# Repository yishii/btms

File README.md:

# Back To the Meeting Switch (BTMS) 【緊急】会議復帰スイッチ

[[日本語版はこちら]](README_ja.md)

## Back Story
Sometimes happen that attending to the online meeting that roughly just listen to. 
This  is the chance for do editing excel or powerpoints.

But, if suddenly asked some comment unexpectedly, then in panic and cannot back to the meeting right away quickly.

That's why we developed Back To the Meeting Switch(BTMS) for this solution.

With the BTMS, you can turn the knob to select the backgrounded online meeting window, then press the knob the meeting windows comes to the forefront, and at the same time, the MIC mute turns off. And just you do is answer with relax.

So, ~~do another job~~ attend the meeting in peace.

## What is BTMS?

BTMS (Back To the Meeting Switch) is a kind of human interface device that using Seeeduino Xiao (SAMD or RP2040).
With this item, we can get back to online meeting right away even though we're doing other things during the online meeting. This is the main purpose of this device. But this has expansion port (compatible with Grove connector)  at the back side of this device and can easily attach some external button as the Dock of BTMS.

For details, plase watch the video below!

## The mechanism

The main operation of this device is just rotate and push the knob. When rotate the knob, this device sends "Alt+TAB" or "Alt+Shift+TAB" according to the rotating direction of the knob for switch to transit to current online meeting window.

After selected the online meeting window now you are attending to, just press the knob to select the window. And at the same time, this device sends the mute toggle key event (Keyboard shortcut) to the selected application.

Mute toggle event is different per video communication applications (e.g. Microsoft Teams, Zoom or Skype, etc).
(For example, Microsoft Teams uses togging the mute by "Ctrl+Shift+M", for WebEx, "Ctrl+M")

So, user set the current communication application to the BTMS and the device uses application-dedicated mute shortcuts for mute toggle key event.

To select the application, just long-press side tactile switch.

## About the expansion port

On the bottom side of the device, there is 5 pin connector for expand the functionality of this device.
The signal of this connector is based on Grove connector (I2C), so that many kind of another interface could be added as a dock.

Now we are developing 6-mechanical-keys-dock for application dedicated controller. (For example, send keyevents specialized for Illustrator, Fusion360, etc.)

## Resources
In this repository there are 3 folders so far.

- hardware<br>
KiCad Design files and schematic in pdf.
- software<br>
Main sourcecode witten in Python(Circuit Python)

Later we'll add 3D Modeling data that could be print out with 3D Printer.

We'll write step-by-step instruction guide later.

This PCBs are created with Seeed FusionPCB!!

## Links

1) Seeed XIAO RP2040: https://www.seeedstudio.com/XIAO-RP2040-v1-0-p-5026.html
2) Seeed Fusion PCBA Service: https://www.seeedstudio.com/pcb-assembly.html
3) Seeed Fusion DIY XIAO Mechanical Keyboard Contest: https://www.seeedstudio.com/seeed-fusion-diy-xiao-mechanical-keyboard-contest.html

## Developers
yishii Twitter : https://twitter.com/yishii

dabyoonig Twitter  : https://twitter.com/dabyoong

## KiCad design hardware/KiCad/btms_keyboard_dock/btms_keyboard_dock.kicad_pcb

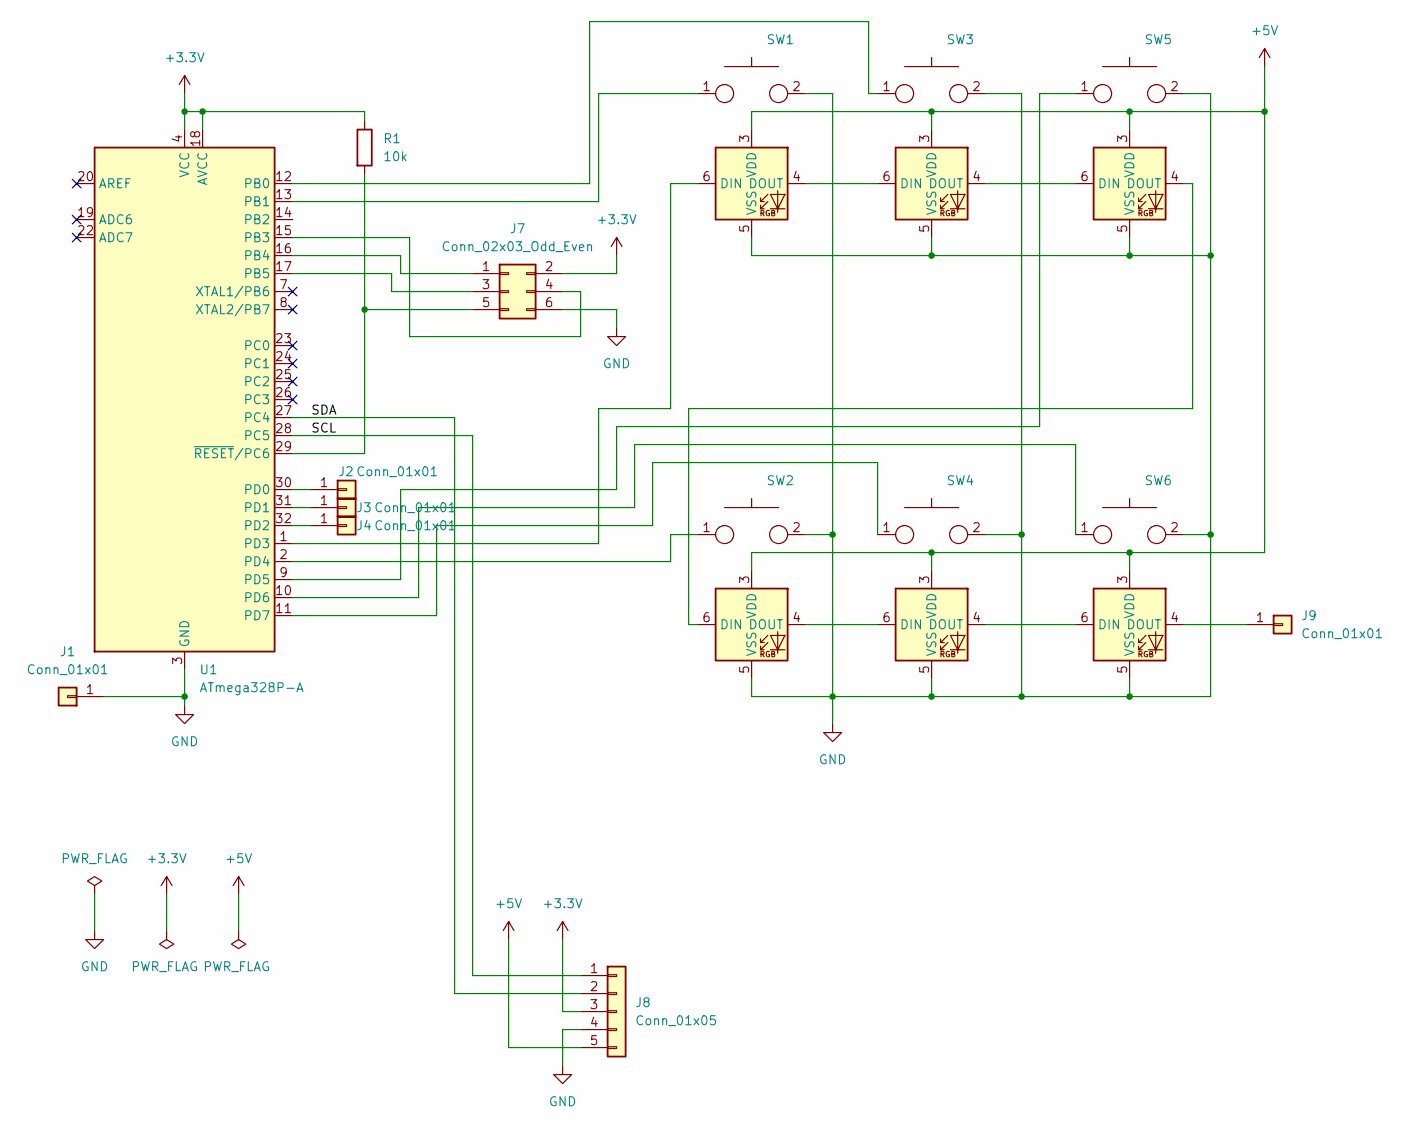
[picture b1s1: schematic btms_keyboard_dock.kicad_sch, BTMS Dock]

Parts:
J1, J2, J3, J4, J9: Conn_01x01; PinHeader_1x01_P2.54mm_Vertical
J7: Conn_02x03_Odd_Even; PinHeader_2x03_P2.54mm_Vertical
J8: Conn_01x05; PinHeader_1x05_P2.54mm_Vertical
R1: 10k; R_0603_1608Metric_Pad0.98x0.95mm_HandSolder
SW1, SW2, SW3, SW4, SW5, SW6: CherryMX_1Pole_wLED; CherryMX_1Pole_wLED_WS2812B
U1: ATmega328P-A; TQFP-32_7x7mm_P0.8mm

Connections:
+3.3V: J7.2, J8.3, R1.1, U1.4 (VCC), U1.6 (VCC), U1.18 (AVCC)
+5V: J8.5, SW1.3 (VDD), SW2.3 (VDD), SW3.3 (VDD), SW4.3 (VDD), SW5.3 (VDD), SW6.3 (VDD)
/SCL: J8.1, U1.28 (PC5)
/SDA: J8.2, U1.27 (PC4)
GND: J1.1, J7.6, J8.4, SW1.2, SW1.5 (VSS), SW2.2, SW2.5 (VSS), SW3.2, SW3.5 (VSS), SW4.2, SW4.5 (VSS), SW5.2, SW5.5 (VSS), SW6.2, SW6.5 (VSS), U1.3 (GND), U1.5 (GND), U1.21 (GND)
unnamed: J2.1, U1.30 (PD0)
unnamed: J3.1, U1.31 (PD1)
unnamed: J4.1, U1.32 (PD2)
unnamed: J7.1, U1.16 (PB4)
unnamed: J7.3, U1.17 (PB5)
unnamed: J7.4, U1.15 (PB3)
unnamed: J7.5, R1.2, U1.29 (~RESET/PC6)
unnamed: J9.1, SW6.4 (DOUT)
unnamed: SW1.1, U1.13 (PB1)
unnamed: SW1.4 (DOUT), SW3.6 (DIN)
unnamed: SW1.6 (DIN), U1.1 (PD3)
unnamed: SW2.1, U1.2 (PD4)
unnamed: SW2.4 (DOUT), SW4.6 (DIN)
unnamed: SW2.6 (DIN), SW5.4 (DOUT)
unnamed: SW3.1, U1.12 (PB0)
unnamed: SW3.4 (DOUT), SW5.6 (DIN)
unnamed: SW4.1, U1.11 (PD7)
unnamed: SW4.4 (DOUT), SW6.6 (DIN)
unnamed: SW5.1, U1.9 (PD5)
unnamed: SW6.1, U1.10 (PD6)

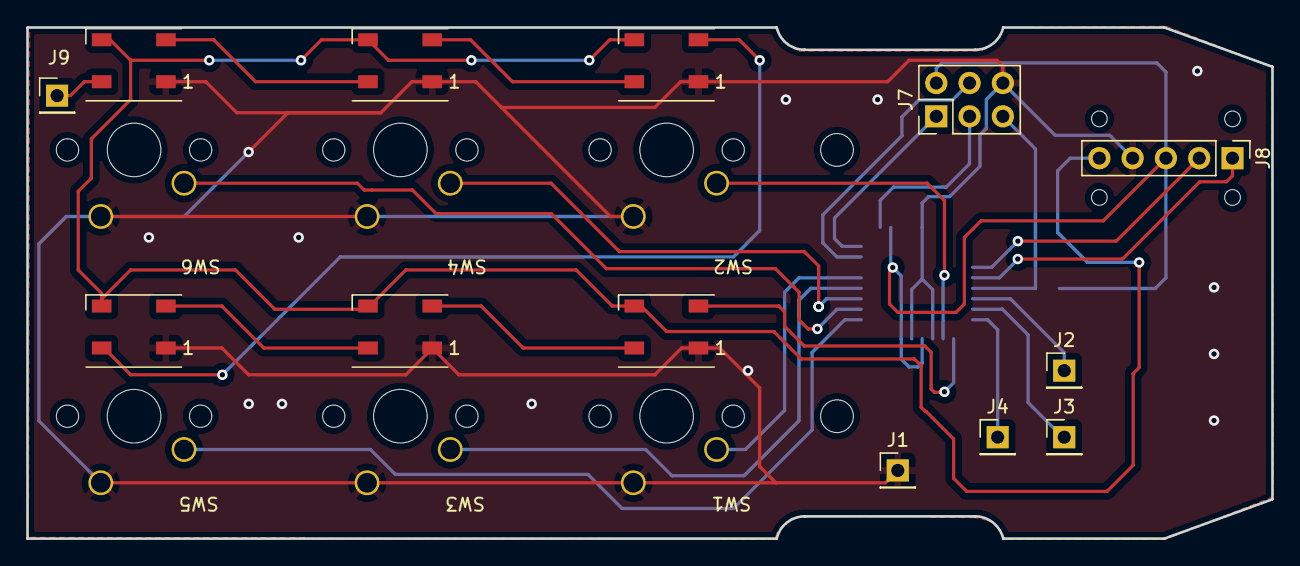
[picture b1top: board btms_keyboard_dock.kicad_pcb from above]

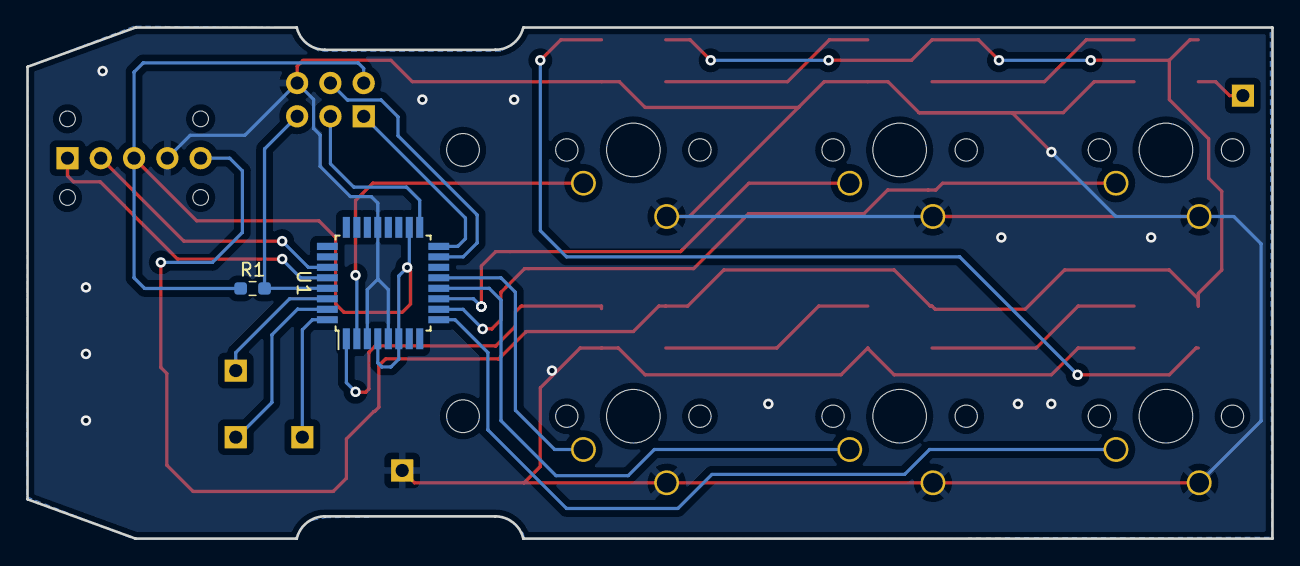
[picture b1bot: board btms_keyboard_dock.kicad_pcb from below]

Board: 2 copper layers, 95.0 x 39.0 mm, 15 parts (2 on the bottom side), 25 nets.

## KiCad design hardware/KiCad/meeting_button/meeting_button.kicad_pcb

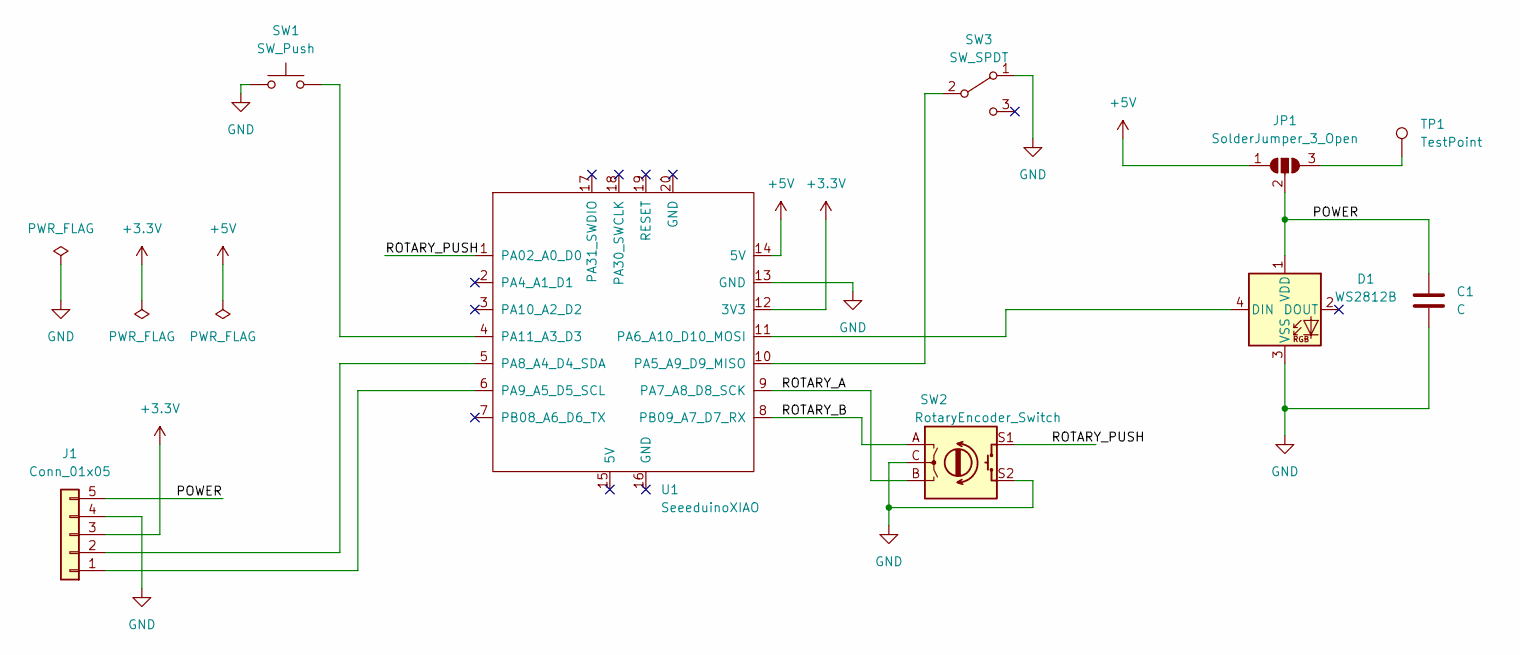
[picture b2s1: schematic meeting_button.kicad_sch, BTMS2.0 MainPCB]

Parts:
C1: C; C_0603_1608Metric
D1: WS2812B; LED_WS2812B_PLCC4_5.0x5.0mm_P3.2mm
J1: Conn_01x05; PinHeader_1x05_P2.54mm_Vertical
JP1: SolderJumper_3_Open; SolderJumper-3_P1.3mm_Open_RoundedPad1.0x1.5mm_NumberLabels
SW1: SW_Push; TactileSwitch_THBP07-043CB
SW2: RotaryEncoder_Switch; Encoder_Bourns_PEC11L
SW3: SW_SPDT; SlideSwitch_SS-12D00-G5
TP1: TestPoint; TestPoint_Pad_1.5x1.5mm
U1: SeeeduinoXIAO; Seeeduino_Xiao_PinHeader

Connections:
+3.3V: J1.3, U1.12 (3V3)
+5V: JP1.1 (A), U1.14 (5V)
/POWER: C1.1, D1.1 (VDD), J1.5, JP1.2 (C)
/ROTARY_A: SW2.B, U1.9 (PA7_A8_D8_SCK)
/ROTARY_B: SW2.A, U1.8 (PB09_A7_D7_RX)
/ROTARY_PUSH: SW2.S1, U1.1 (PA02_A0_D0)
GND: C1.2, D1.3 (VSS), J1.4, SW1.1, SW2.C, SW2.S2, SW3.1 (A), U1.13 (GND)
unnamed: D1.4 (DIN), U1.11 (PA6_A10_D10_MOSI)
unnamed: J1.1, U1.6 (PA9_A5_D5_SCL)
unnamed: J1.2, U1.5 (PA8_A4_D4_SDA)
unnamed: JP1.3 (B), TP1.1
unnamed: SW1.2, U1.4 (PA11_A3_D3)
unnamed: SW3.2 (B), U1.10 (PA5_A9_D9_MISO)

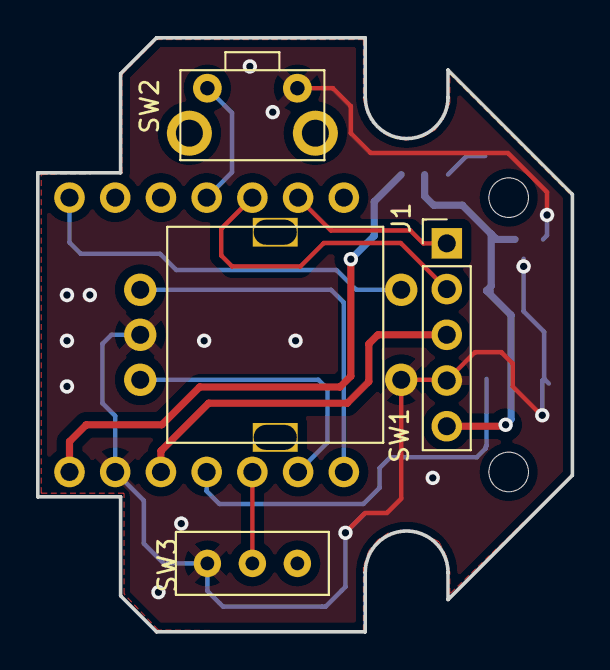
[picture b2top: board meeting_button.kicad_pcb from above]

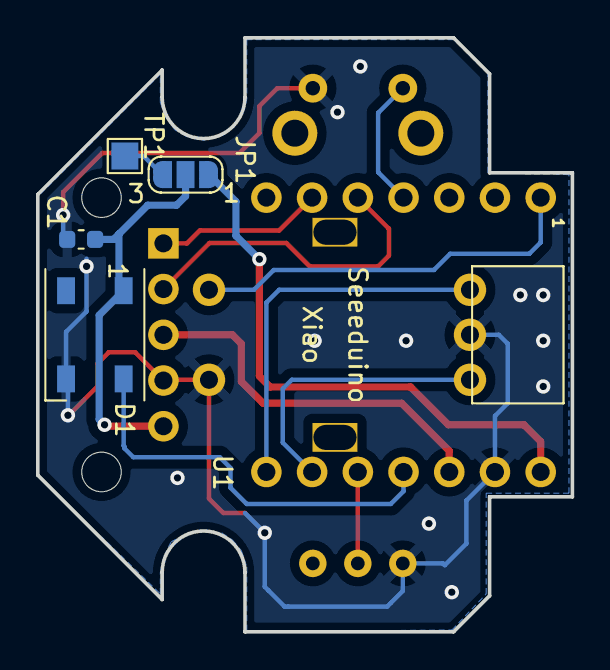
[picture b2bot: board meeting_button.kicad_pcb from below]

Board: 2 copper layers, 29.7 x 33.0 mm, 9 parts (5 on the bottom side), 13 nets.

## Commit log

2022-10-11 説明を作成
2022-10-11 YouTubeリンク修正
2022-10-11 もっかい修正
2022-10-11 fix description about instrction guide
2022-10-11 説明微修正
2022-10-11 画像を更新
2022-10-12 Added links
2022-10-12 Change pin assignment
2022-10-12 added pcba pictures
2022-10-12 change picture
2022-10-13 test(! to !!)
2022-10-13 caseのstlをアップ。導光部もstl形式にしています。
2022-10-13 unitの画像を更新
2022-10-13 unit画像をさらに更新
2022-10-13 unit部分を更新した動画に差し替え
2022-10-14 6button dockのテスト用プログラム
2022-10-15 6botton dock FW First commit
2022-10-20 Caseのデータを更新（コネクタ周り、ボタン周り）
2022-10-26 update to add back story
2022-10-26 added developers
2022-10-26 modify comment
2022-10-26 modified comment
2022-10-27 日本語版を追加
2022-10-27 日本語英語ページリンクを更新
2022-11-20 Updated to support 6keys dock
2022-11-20 LEDカラーを更新
2022-11-20 Fnキーサポート版コードベースを作成
2022-11-30 各アプリの制御をレイヤクラスと個々のレイヤごとのソースで行うよう改変 アプリモード(PC側から制御する動作モード)用の実装
2022-12-01 add shortcut key
2022-12-01 set color
2022-12-01 Zoom_color_reset
